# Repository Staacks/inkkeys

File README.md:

# inkkeys
Details and instructions can be found on https://there.oughta.be/a/macro-keyboard

In contrast to most of my other projects, I decided to put this into its own repository as it is slightly more complex and I am hoping for community contributions.

If you have pull-requests, bug reports or want to contribute new case designs, please do not hesitate to open an issue. For generic discussions, "show and tell" and if you are looking for support for something that is not a problem in the code here, I would recommend [r/thereoughtabe on reddit](https://www.reddit.com/r/thereoughtabe/).

## Common problems

### Display revision 2
Apparently, the original design used revision 1 of the display, while many newly ordered version are revision 2. There are a few differences and thankfully, [Corky402 made a good list of required changes on Reddit](https://www.reddit.com/r/arduino/comments/l4wxxf/the_hardware_is_assembled_and_passed_all_tests/gqovq1j?utm_source=share&utm_medium=web2x&context=3). Here is an excerpt of the original post for reference:
>If you want to test your display hooked to a Arduino or Raspberry Pi you need to run examples for the epd2in9_V2 not the epd2in9.
>
>To get this awesome project working there is no need to make any alterations to the PCB, just simply plumb the Waveshare up on the connectors as I describe, not as per Sebastian's original post.
>
>PCB Pin Waveshare wiring loom
>
>+5v Grey
>
>GND Brown
>
>DIN Blue
>
>CLK Yellow
>
>CS Orange
>
>DC Green
>
>RST Purple
>
>BUSY White
>
>In short you are swapping the RST & BUSY lines on the PCB.
>
>Next, go to your Arduino sketch. This is for the hardware-test script. Enable line numbering and go to line 43 which reads -
>
```c
GxEPD2_290 display(/*CS=*/ PIN_CS, /*DC=*/ PIN_DC, /*RST=*/ PIN_RST, /*BUSY=*/ PIN_BUSY);
```
>
>Change this to -

```c
GxEPD2_290_T94 display(/*CS=*/ PIN_CS, /*DC=*/ PIN_DC, /*RST=*/ PIN_RST, /*BUSY=*/ PIN_BUSY);
```

>Then go to settings.h
>
>Lines 2 - 7 need to be altered so change that section of code as follows -
```c
const byte PIN_DIN = 16;
const byte PIN_CLK = 15;
const byte PIN_CS = 19;
const byte PIN_DC = 18;
const byte PIN_RST = 10;
const byte PIN_BUSY = 14;
```
>
>The sketch will then compile and when uploaded to the board you will get the Waveshare drawing all sorts of Austin Powers time machine circles that make your eyes spin! 

The class change above applies to the hardware test. In the main inkkeys sketch, set `#define DISPLAY_REVISION 2` in `settings.h` instead (and swap the RST and BUSY pins there as shown above). This selects `GxEPD2_290_T94_V2` together with a partial refresh waveform tuned for this panel. With the stock waveform, partial refreshes on revision 2 leave grey ghosts of previous images and unchanged black areas fade (see [#16](https://github.com/Staacks/inkkeys/issues/16)).

If partial refreshes on your display still look grey, or smear the edges of icons, adjust `PARTIAL_REFRESH_REPEATS` in `settings.h` (3 by default, more drives harder but takes ~0.25s longer per step). You can try values without flashing by sending `R p <repeats>` over the serial connection instead of `R p`.

## Gallery

Original design as presented on there.oughta.be with the 3d printing files from this repository.

Design by John, Mat and Roland from the UK. The case was CNC milled from beech with a similarly machined clear perspex lid. You can find the knob with finger dimple by Roland Irving in the 3dprint folder as know_with_dimple.stl.

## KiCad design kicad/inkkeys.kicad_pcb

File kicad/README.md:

# Alternative layouts and PCB designs

Modifications by user are linked below:
* [SMD version by dschiedsch](https://github.com/dschiedsch/inkkeys) Similar to the orignal, but LEDs, resistors and capacitors are SMD components.

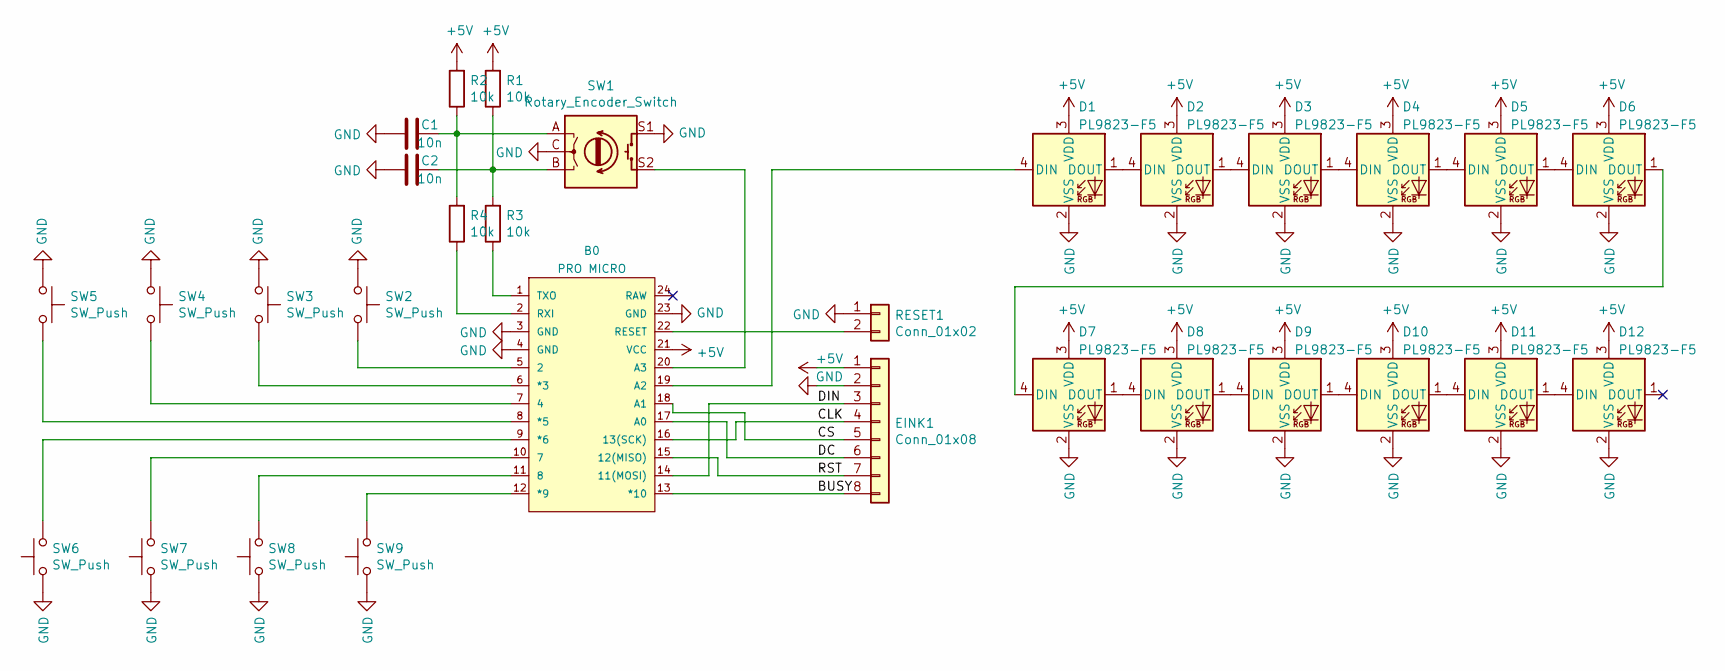
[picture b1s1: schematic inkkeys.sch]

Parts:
B0: PRO MICRO; SPARKFUN_PRO_MICRO
C1, C2: 10n; C_Disc_D5.0mm_W2.5mm_P5.00mm
D1, D2, D3, D4, D5, D6, D7, D8, D9, D10, D11, D12: PL9823-F5; LED_D5.0mm-4_RGB
EINK1: Conn_01x08; PinHeader_1x08_P2.54mm_Vertical
R1, R2, R3, R4: 10k; R_Axial_DIN0207_L6.3mm_D2.5mm_P10.16mm_Horizontal
RESET1: Conn_01x02; PinHeader_1x02_P2.54mm_Vertical
SW1: Rotary_Encoder_Switch; RotaryEncoder_Alps_EC11E-Switch_Vertical_H20mm
SW2, SW3, SW4, SW5, SW6, SW7, SW8, SW9: SW_Push; SW_Cherry_MX_1.00u_PCB

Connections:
+5V: B0.21 (VCC), D1.3 (VDD), D2.3 (VDD), D3.3 (VDD), D4.3 (VDD), D5.3 (VDD), D6.3 (VDD), D7.3 (VDD), D8.3 (VDD), D9.3 (VDD), D10.3 (VDD), D11.3 (VDD), D12.3 (VDD), EINK1.1, R1.2, R2.2; also elsewhere on the board
/BUSY: B0.13 (*10), EINK1.8; also elsewhere on the board
/CLK: B0.16 (13(SCK)), EINK1.4; also elsewhere on the board
/CS: B0.18 (A1), EINK1.5; also elsewhere on the board
/DC: B0.17 (A0), EINK1.6; also elsewhere on the board
/DIN: B0.14 (11(MOSI)), EINK1.3; also elsewhere on the board
/RST: B0.15 (12(MISO)), EINK1.7; also elsewhere on the board
GND: B0.3 (GND), B0.4 (GND), B0.23 (GND), C1.2, C2.2, D1.2 (VSS), D2.2 (VSS), D3.2 (VSS), D4.2 (VSS), D5.2 (VSS), D6.2 (VSS), D7.2 (VSS), D8.2 (VSS), D9.2 (VSS), D10.2 (VSS), D11.2 (VSS), D12.2 (VSS), EINK1.2, RESET1.1, SW1.C, SW1.S1, SW2.1, SW3.1, SW4.1, SW5.1, SW6.1, SW7.1, SW8.1, SW9.1; also elsewhere on the board
unnamed: B0.1 (TXO), R3.1
unnamed: B0.2 (RXI), R4.1
unnamed: B0.5 (2), SW2.2
unnamed: B0.6 (*3), SW3.2
unnamed: B0.7 (4), SW4.2
unnamed: B0.8 (*5), SW5.2
unnamed: B0.9 (*6), SW6.2
unnamed: B0.10 (7), SW7.2
unnamed: B0.11 (8), SW8.2
unnamed: B0.12 (*9), SW9.2
unnamed: B0.19 (A2), D1.4 (DIN)
unnamed: B0.20 (A3), SW1.S2
unnamed 20: B0.22 (RESET), RESET1.2; also elsewhere on the board
unnamed: C1.1, R2.1, R4.2, SW1.A
unnamed: C2.1, R1.1, R3.2, SW1.B
unnamed: D1.1 (DOUT), D2.4 (DIN)
unnamed: D2.1 (DOUT), D3.4 (DIN)
unnamed: D3.1 (DOUT), D4.4 (DIN)
unnamed: D4.1 (DOUT), D5.4 (DIN)
unnamed: D5.1 (DOUT), D6.4 (DIN)
unnamed: D6.1 (DOUT), D7.4 (DIN)
unnamed: D7.1 (DOUT), D8.4 (DIN)
unnamed: D8.1 (DOUT), D9.4 (DIN)
unnamed: D10.1 (DOUT), D11.4 (DIN)
unnamed: D9.1 (DOUT), D10.4 (DIN)
unnamed: D11.1 (DOUT), D12.4 (DIN)

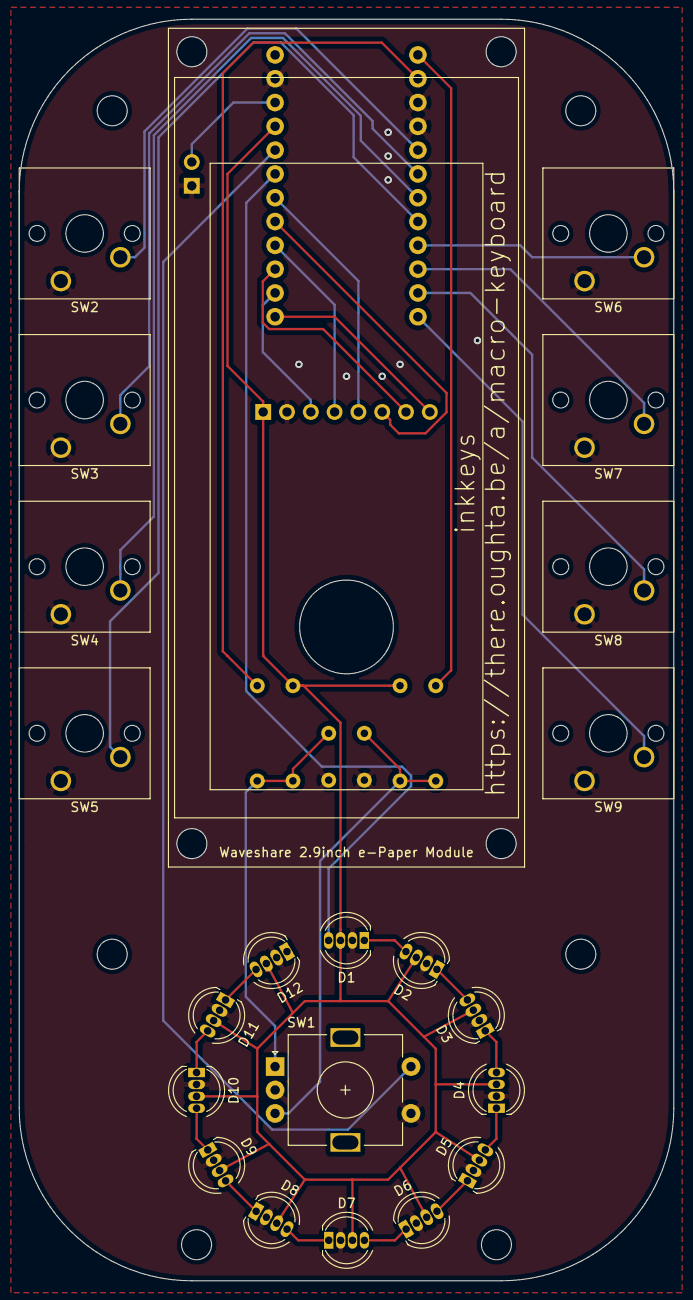
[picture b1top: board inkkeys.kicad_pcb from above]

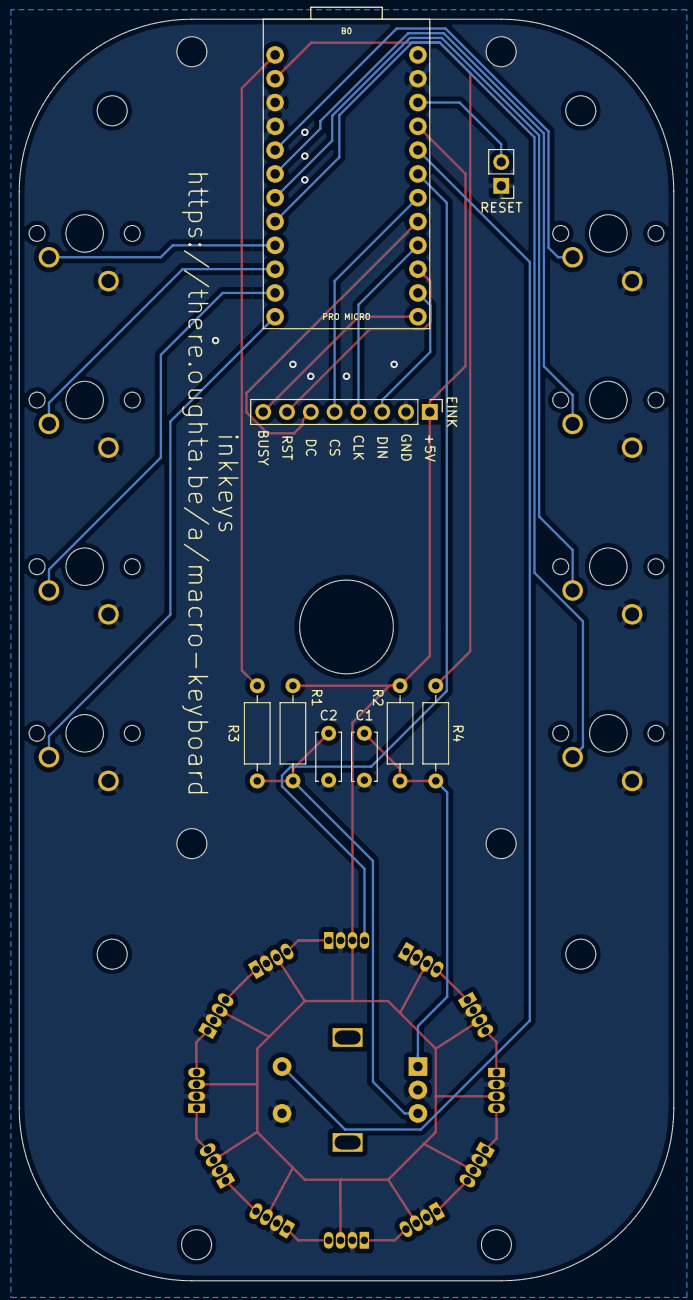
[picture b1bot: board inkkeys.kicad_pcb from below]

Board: 2 copper layers, 69.9 x 134.6 mm, 30 parts (9 on the bottom side), 34 nets.

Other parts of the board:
EINK: Conn_01x08; PinHeader_1x08_P2.54mm_Vertical
RESET: Conn_01x02; PinHeader_1x02_P2.54mm_Vertical

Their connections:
+5V: EINK.1; also elsewhere on the board
/BUSY: EINK.8; also elsewhere on the board
/CLK: EINK.4; also elsewhere on the board
/CS: EINK.5; also elsewhere on the board
/DC: EINK.6; also elsewhere on the board
/DIN: EINK.3; also elsewhere on the board
/RST: EINK.7; also elsewhere on the board
GND: EINK.2, RESET.1; also elsewhere on the board
unnamed 20: RESET.2; also elsewhere on the board

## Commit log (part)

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2021-02-08 Initial commit, preparing for publication.
2021-02-12 Fix: Polling, better serial input, memory leak / slowdown after many window requests.
2021-02-20 Added the blend file from which the STL files were exported.
2021-04-14 Add a little gallery to showcase different builds of the macro keyboard.
2021-05-27 Added know with finger dimple by Roland Irving.
2022-01-11 Update README.md
    Some of the code gets lost in Markdown, just adding code blocks around it so you can see what the correct content is.
2022-01-24 Update configurations for waveshare v2 and alternative pro micro
2022-03-12 mentions of alternative display classes
